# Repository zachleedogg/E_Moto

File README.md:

# E_Moto
Electric Motorcycle Project

This Repo Contains everything related to the E-Moto build.

Architecture inlcudes everything from block diagrams of the system level, design calculations, reseach link to off-the-shelf parts, and anything else that isn't strict design work.

CAD includes mechanical CAD files (mostly Solid Works) of various custom parts of the bike. Also includes some side-projects and also tools that are relevant to this project.

Firware is the Embeded code that targets the dsPIC33 processor used in the Electronics. I would like to switch to an STM32 based system but its a little late for that now.

Hardware is Electrical Hardware designs based on KiCad. There are more projects started than will probably be finished here but thats ok!

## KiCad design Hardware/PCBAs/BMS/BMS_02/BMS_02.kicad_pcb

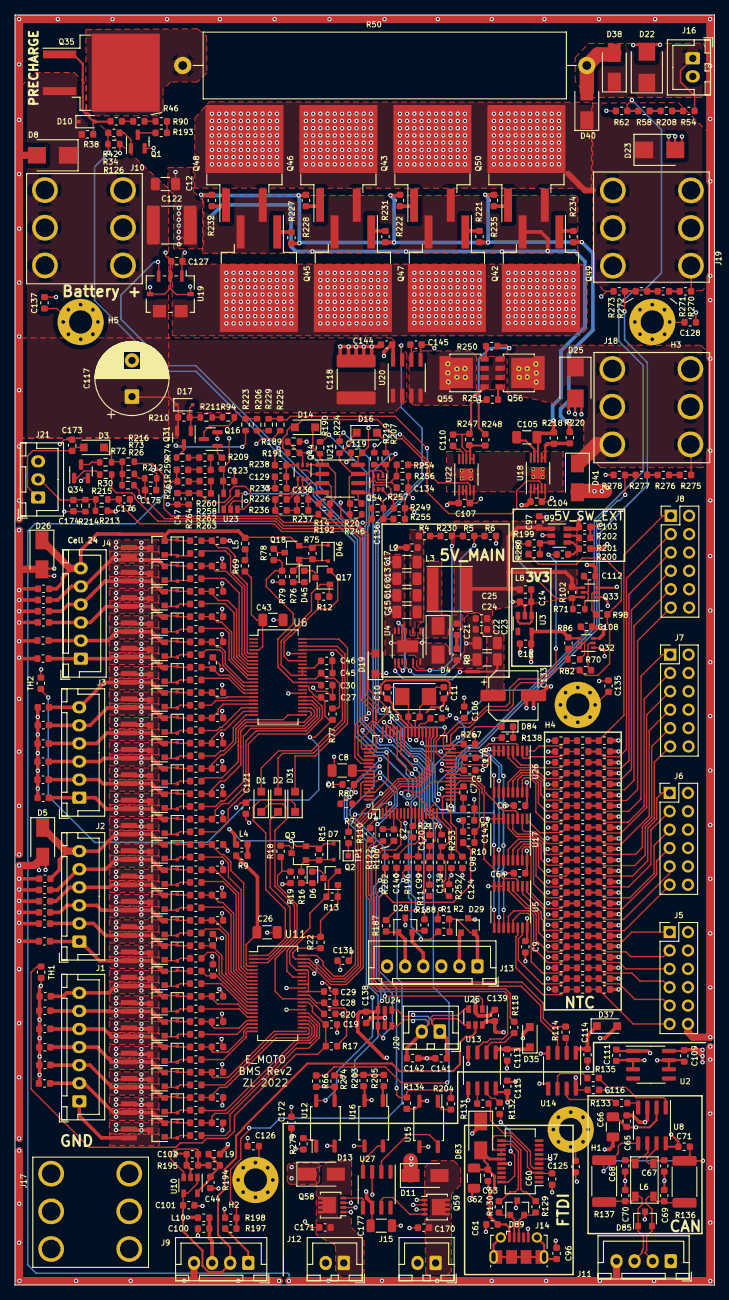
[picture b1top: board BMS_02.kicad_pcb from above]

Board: 4 copper layers, 96.7 x 175.6 mm, 621 parts (0 on the bottom side), 396 nets.

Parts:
C1, C2, C3, C4, C5, C6, C7, C9, C14, C18, C19, C20, C24, C27, C30, C31, C32, C33, C34, C35, C36, C37, C38, C39, C40, C41, C42, C44, C47, C48, C49, C50, C51, C52, C53, C54, C55, C56, C57, C58, C59, C60, C63, C64, C96, C97, C99, C101, C102, C103, C104, C107, C108, C109, C111, C112, C113, C114, C115, C116, C119, C123, C130, C136, C138, C139, C140, C141, C142, C143, C146, C147, C148, C149, C150, C151, C152, C153, C154, C155, C156, C157, C158, C159, C160, C161, C162, C163, C164, C165, C166, C167, C168, C169, C170, C171: 100nF; C_0603_1608Metric
C8, C22, C23, C105: 10uF; C_1206_3216Metric
C10, C11, C21, C67, C68, C69, C70, C145: 18pF; C_0603_1608Metric
C12, C13, C15, C16, C17, C26, C43: 100nF; C_1206_3216Metric
C25, C61, C65, C71, C72, C73, C74, C75, C76, C77, C78, C79, C80, C81, C82, C83, C84, C85, C86, C87, C88, C89, C90, C91, C92, C93, C94, C95, C98, C106, C120, C121, C124, C125, C126, C127, C128, C131, C132, C135, C137, C172, C173, C174, C175, C176, C178: 10nF; C_0603_1608Metric
C28, C29, C45, C46, C100, C110, C144: 1uF; C_0603_1608Metric
C62, C66, C177: 4u7; C_1206_3216Metric
C117: 22u; CP_Radial_D10.0mm_P5.00mm
C118, C122: 1u; C_2220_5650Metric
C129, C134: 1nF; C_0603_1608Metric
C133: 47u; CP_Elec_6.3x5.9
D1, D2, D3, D14, D16, D19, D31, D35, D37: D_Schottky; D_SOD-123F
D4, D11, D13, D38, D40, D41, D83: D_Schottky; D_SMA
D5, D26: D_TVS; D_SMA
D6, D45, D84: D_LED; D_0603_1608Metric
D7, D9, D10, D12, D15, D17, D18, D21, D24, D27, D30, D33, D36, D39, D42, D46, D48, D51, D54, D57, D60, D63, D66, D69, D72, D75, D78, D81: 12V; D_SOD-323F
D8, D22, D23, D25: D_TVS; D_SMB
D28, D29, D85, D89: D_Schottky_Dual_CommonAnode_AKK; D_SOT-23_ANK
H1, H2, H3, H4, H5: MountingHole_Pad; MountingHole_3.2mm_M3_Pad_Via
J1: Conn_01x07; JST_XH_B7B-XH-A_1x07_P2.50mm_Vertical
J2, J3, J4, J13: Conn_01x06; JST_XH_B6B-XH-A_1x06_P2.50mm_Vertical
J5, J6, J7, J8: Conn_02x06_Odd_Even; PinHeader_2x06_P2.54mm_Vertical
J9, J11: Conn_01x04; JST_XH_B4B-XH-A_1x04_P2.50mm_Vertical
J10, J17, J18, J19: 7807
J12, J15, J16, J20: Conn_01x02; JST_XH_B2B-XH-A_1x02_P2.50mm_Vertical
J14: USB_B_Micro; USB_Micro-B_Molex-105017-0001
J21: Conn_01x04; JST_XH_B3B-XH-A_1x03_P2.50mm_Vertical
L1, L2, L4, L5, L8, L9, L10: L_Ferrite; L_0603_1608Metric
L3: 47u; Inductor_Taiyo-Yuden_NR-60xx
L6: L_Coupled; ACT45B
NT1: Net-Tie_2; Net_Tie-0.5mm
Q1, Q2, Q16, Q17, Q34: Q_NMOS_GSD; SOT-23
Q3, Q4, Q5, Q6, Q7, Q8, Q9, Q10, Q11, Q12, Q13, Q14, Q15, Q18, Q19, Q20, Q21, Q22, Q23, Q24, Q25, Q26, Q27, Q28, Q29, Q30, Q31: Q_PMOS_GSD; SOT-23
Q32, Q33, Q44, Q54: Q_DUAL_NMOS_PMOS; SOT-363_SC-70-6
Q35: Q_PMOS_GDS; TO-263-2
Q42, Q43, Q45, Q46, Q47, Q48, Q49, Q50: NTB5D0N15MC; TO-263-2
Q55, Q56: TPH3300CNH,L1Q; POWER_SO8
Q58, Q59: RQ3G100GNTB; LFPAK33
R1, R2, R10, R12, R13, R15, R34, R66, R70, R71, R75, R80, R86, R102, R122, R126, R134, R139, R140, R141, R142, R143, R144, R145, R146, R147, R148, R149, R150, R151, R152, R153, R154, R155, R156, R157, R158, R159, R160, R161, R162, R163, R164, R165, R166, R167, R168, R169, R170, R171, R172, R173, R174, R175, R176, R177, R178, R179, R180, R181, R182, R183, R184, R185, R186, R189, R191, R192, R194, R195, R196, R197, R200, R201, R203, R207, R215, R217, R219, R226, R233, R237, R238, R246, R249, R253, R254, R255, R267, R274, R279, R280, R282: 10k0; R_0603_1608Metric
R3, R4, R14, R20, R54, R58, R74, R206, R208, R223, R225, R264, R270, R271, R272, R275, R276, R277: 1M; R_0603_1608Metric
R5, R16, R76: 32k0; R_0603_1608Metric
R6: 13k0; R_0603_1608Metric
R7, R23, R27, R30, R31, R35, R39, R43, R47, R51, R55, R59, R63, R67, R82, R83, R87, R91, R95, R98, R99, R103, R106, R107, R110, R111, R114, R115, R118, R119, R123, R127, R131, R132, R133, R135, R138, R187, R188, R199, R204, R205, R209: 100R; R_0603_1608Metric
R8, R202, R220, R221, R222, R227, R228, R231, R232, R234, R235, R248, R250, R251: 3R3; R_0603_1608Metric
R9, R69, R129, R130: 20R0; R_0603_1608Metric
R11, R198, R236, R252, R256: 19k6; R_0603_1608Metric
R17, R38, R42, R46, R62, R77, R90, R190, R193, R210, R216, R224, R229, R257, R273, R278: 100k; R_0603_1608Metric
R18, R78, R94, R211, R218, R230, R247: 499k; R_0603_1608Metric
R19, R79: 26k1 0.1%; R_0603_1608Metric
R21, R25, R29, R33, R37, R41, R45, R49, R53, R57, R61, R65, R81, R85, R89, R93, R97, R101, R105, R109, R113, R117, R121, R125: 15R0; Resistor_SMD_0805_Wide
R22: 1k8; R_0603_1608Metric
R24, R28, R32, R36, R40, R44, R48, R52, R56, R60, R64, R68, R84, R88, R92, R96, R100, R104, R108, R112, R116, R120, R124, R128: 3k3; R_0603_1608Metric
R26, R73: 4k7; R_0603_1608Metric
R50: 100R; R_Axial_Power_L50.0mm_W9.0mm_P55.88mm
R72, R212: 1k3; R_0603_1608Metric
R136, R137: 60R; R_2512_6332Metric
R213, R214: 330R; R_0603_1608Metric
R258, R259, R260, R261, R262, R263: 10M; R_0603_1608Metric
TH1, TH2: Thermistor_NTC; R_0603_1608Metric
TP1: TestPoint; TestPoint_Pad_1.0x1.0mm
U1: PIC33EP256MC506; TQFP-64_10x10mm_P0.5mm
U2: LM2931-5.0_SO8; SOIC-8_3.9x4.9mm_P1.27mm
U3: TPS73633DBV; SOT-23-5
U4: LTC3638; Linear_MSOP-12-16-1EP_3x4mm_P0.5mm
U5, U17, U26: CD4051B; TSSOP-16_4.4x5mm_P0.65mm
U6, U11: LTC6802-1; SSOP-44_5.3x12.8mm_P0.5mm
U7: FT231XS; SSOP-20_3.9x8.7mm_P0.635mm
U8: MCP2562-E-SN; SOIC-8_3.9x4.9mm_P1.27mm
U9: TPS2551-Q1; SOT-23-6
U10, U23: OPA320-Q1; SOT-23-5
U12, U15, U16: TLX9185A(GBTPL,F; SO-4_4.4x3.9mm_P2.54mm
U13, U14: ADUM1281ARZ-RL7; SOIC-8_3.9x4.9mm_P1.27mm
U18, U22: LTC7001; MSOP-10-1EP_3x3mm_P0.5mm_EP1.68x1.88mm_ThermalVias
U19: ACS72981LLRATR-100B5; Allegro_PSOF-7_4.8x6.4mm_P1.60mm
U20: CT415-HSN820DR; SOIC-8_3.9x4.9mm_P1.27mm
U21: LMV393; SOIC-8_3.9x4.9mm_P1.27mm
U24, U25: INA181; SOT-23-6
U27: FAN3216TMX-F085; SOIC-8_3.9x4.9mm_P1.27mm
Y1: 8MHz; Crystal_SMD_5032-2Pin_5.0x3.2mm

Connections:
5V_SW_nFAULT: R200.2, U1.31 (SDA2/RPI24/RA8)
12V_POWER: C109.1, D11.1 (K), D13.1 (K), J11.1, J12.2, J15.2, R279.2, U2.8 (IN)
12V_POWER_STATUS: R66.1, U1.42 (RD8)
+3.3VA: C108.1, C123.1, C138.1, C139.1, D35.2 (A), D37.2 (A), L9.2, Q32.3, Q44.4, Q54.4, R80.1, R122.1, R140.1, R142.1, R144.1, R146.1, R148.1, R150.1, R152.1, R154.1, R156.1, R158.1, R160.1, R162.1, R164.1, R166.1, R168.1, R170.1, R172.1, R174.1, R176.1, R178.1, R180.1, R182.1, R184.1, R186.1, R192.2, R201.1, R209.1, R226.2, R236.1, R246.2, R249.2, R255.1, U23.5 (Vcc), U24.6 (V+), U25.6 (V+)
+3V3: C1.1, C2.1, C3.1, C4.1, C5.1, C18.1, D19.1 (K), D29.2 (K), J13.2, L1.2, Q32.4, R1.1, R86.2, U1.10 (Vdd), U1.26 (Vdd), U1.38 (Vdd), U1.57 (Vdd), U3.5 (OUT), U12.4
+5V: C22.1, C23.1, C24.1, C25.1, C97.1, C133.1, L3.2, L8.2, NT1.2, Q33.4, R102.2, U9.1 (IN)
+5VA: C6.1, C9.1, C64.1, C104.1, C107.1, C112.1, C119.1, C127.1, C144.1, Q33.3, U5.16 (VDD), U17.16 (VDD), U18.1 (VCC), U19.1 (VCC), U20.8 (VCC), U21.8 (V+), U22.1 (VCC), U26.16 (VDD)
+5VL: C65.1, C66.2, C111.1, C115.1, C116.1, C177.2, D83.1 (K), U2.1 (OUT), U8.3 (VDD), U13.8 (VDD2), U14.8 (VDD2), U27.6 (VDD)
+5VP: C103.1, L10.2, R213.1, U9.6 (OUT)
+BATT: C12.1, C117.1, C118.1, C122.1, D8.1 (K), D10.1 (K), D17.1 (K), J10.1, L2.2, Q31.2 (S), Q35.3 (S), R38.2, R210.1, U19.5 (IP+), U20.1 (IP+), U20.2 (IP+)
/TopLevel/ChargerAndDCDC/HV_dcdc_gate: R248.2, R250.1, R251.1
/TopLevel/ChargerAndDCDC/HV_dcdc_shunt: Q55.5 (D), U20.3 (IP-), U20.4 (IP-)
/TopLevel/ChargerAndDCDC/HV_dcdc_source: C110.2, Q55.1 (S), Q55.2 (S), Q55.3 (S), Q56.1 (S), Q56.2 (S), Q56.3 (S), R247.2, U22.8 (TS)
/TopLevel/ChargerAndDCDC/HV_ev_g: R220.2, R221.1, R222.1, R227.1, R228.1, R231.1, R232.1, R234.1, R235.1
/TopLevel/ChargerAndDCDC/HV_ev_shunt: Q42.2 (D), Q45.2 (D), Q47.2 (D), Q49.2 (D), U19.6 (IP-)
/TopLevel/ChargerAndDCDC/HV_ev_source: C105.2, Q42.3 (S), Q43.3 (S), Q45.3 (S), Q46.3 (S), Q47.3 (S), Q48.3 (S), Q49.3 (S), Q50.3 (S), R218.2, U18.8 (TS)
/TopLevel/ChargerAndDCDC/dcdc_i: R253.1, R254.1, U20.7 (VIOUT)
/TopLevel/Communications/CAN_FILT_N: C68.2, L6.3, U8.6 (CANL)
/TopLevel/Communications/CAN_FILT_P: C67.2, L6.1, U8.7 (CANH)
/TopLevel/Contactor/HV_precharge_gate: D10.2 (A), Q35.1 (G), R38.1, R42.2
/TopLevel/Contactor/HV_precharge_switch: Q35.2 (D), R50.2
/TopLevel/Contactor/c1_in: U15.4, U27.2 (INA)
/TopLevel/Contactor/c1_out: Q59.4 (G), U27.7 (~OUTA)
/TopLevel/Contactor/c2_in: U16.4, U27.4 (INB)
/TopLevel/Contactor/c2_out: Q58.4 (G), U27.5 (~OUTB)
/TopLevel/IsolationDetection/HV_VBUS_ISO_SW: Q31.3 (D), R74.1, R206.2
/TopLevel/PowerRails/5V_N_SW_EN: Q33.6, R71.1, R102.1, R199.2
/TopLevel/PowerRails/FB_5V: NT1.1, U4.9 (VFB)
/TopLevel/PowerRails/HV_VBATT_FILT_5V_IN: C13.1, C15.1, C16.1, C17.1, L2.1, R4.1, U4.3 (VIN)
/TopLevel/PowerRails/SWITCH_NODE_5V: C21.1, D4.1 (K), L3.1, U4.1 (SW)
/TopLevel/Stack_1/5V_ref_LTC6802: C28.1, R17.2, U11.33 (Vref)
/TopLevel/Stack_1/Bank_1/C: C34.1, R35.1, U11.27 (C1)
/TopLevel/Stack_1/Bank_1/S: R36.1, U11.28 (S1)
/TopLevel/Stack_1/Bank_2/C: C33.1, R31.1, U11.25 (C2)
/TopLevel/Stack_1/Bank_2/S: R32.1, U11.26 (S2)
/TopLevel/Stack_1/Bank_3/C: C32.1, R27.1, U11.23 (C3)
/TopLevel/Stack_1/Bank_3/S: R28.1, U11.24 (S3)
/TopLevel/Stack_1/Bank_4/C: C31.1, R23.1, U11.21 (C4)
/TopLevel/Stack_1/Bank_4/S: R24.1, U11.22 (S4)
/TopLevel/Stack_1/Bank_5/C: C35.1, R39.1, U11.19 (C5)
/TopLevel/Stack_1/Bank_5/S: R40.1, U11.20 (S5)
/TopLevel/Stack_1/Bank_6/C: C36.1, R43.1, U11.17 (C6)
/TopLevel/Stack_1/Bank_6/S: R44.1, U11.18 (S6)
/TopLevel/Stack_1/Bank_7/C: C37.1, R47.1, U11.15 (C7)
/TopLevel/Stack_1/Bank_7/S: R48.1, U11.16 (S7)
/TopLevel/Stack_1/Bank_8/C: C38.1, R51.1, U11.13 (C8)
/TopLevel/Stack_1/Bank_8/S: R52.1, U11.14 (S8)
/TopLevel/Stack_1/Bank_9/S: R56.1, U11.12 (S9)
/TopLevel/Stack_1/Bank_10/C: C40.1, R59.1, U11.9 (C10)
/TopLevel/Stack_1/Bank_10/C-1: C39.1, R55.1, U11.11 (C9)
/TopLevel/Stack_1/Bank_10/S: R60.1, U11.10 (S10)
/TopLevel/Stack_1/Bank_11/C: C41.1, R63.1, U11.7 (C11)
/TopLevel/Stack_1/Bank_11/S: R64.1, U11.8 (S11)
/TopLevel/Stack_1/Bank_12/C: C42.1, R67.1, U11.5 (C12)
/TopLevel/Stack_1/Bank_12/S: R68.1, U11.6 (S12)
/TopLevel/Stack_1/SCBO: D31.1 (K), U11.1 (CSBO)
/TopLevel/Stack_1/SCKO: D1.1 (K), U11.3 (SCKO)
/TopLevel/Stack_1/SDIO: D2.1 (K), U11.2 (SDOI)
/TopLevel/Stack_1/Vreg: C29.1, Q2.1 (G), R13.1, R22.2, U11.34 (Vreg), U11.36 (MMB), U11.40 (Vmode)
/TopLevel/Stack_2/5V_ref_LTC6802: C45.1, R77.2, U6.33 (Vref)
/TopLevel/Stack_2/Bank_1/C: C51.1, R95.1, U6.27 (C1)
/TopLevel/Stack_2/Bank_1/S: R96.1, U6.28 (S1)
/TopLevel/Stack_2/Bank_2/C: C50.1, R91.1, U6.25 (C2)
/TopLevel/Stack_2/Bank_2/S: R92.1, U6.26 (S2)
/TopLevel/Stack_2/Bank_3/C: C49.1, R87.1, U6.23 (C3)
/TopLevel/Stack_2/Bank_3/S: R88.1, U6.24 (S3)
/TopLevel/Stack_2/Bank_4/C: C48.1, R83.1, U6.21 (C4)
/TopLevel/Stack_2/Bank_4/S: R84.1, U6.22 (S4)
/TopLevel/Stack_2/Bank_5/C: C52.1, R99.1, U6.19 (C5)
/TopLevel/Stack_2/Bank_5/S: R100.1, U6.20 (S5)
/TopLevel/Stack_2/Bank_6/C: C53.1, R103.1, U6.17 (C6)
/TopLevel/Stack_2/Bank_6/S: R104.1, U6.18 (S6)
/TopLevel/Stack_2/Bank_7/C: C54.1, R107.1, U6.15 (C7)
/TopLevel/Stack_2/Bank_7/S: R108.1, U6.16 (S7)
/TopLevel/Stack_2/Bank_8/C: C55.1, R111.1, U6.13 (C8)
/TopLevel/Stack_2/Bank_8/S: R112.1, U6.14 (S8)
/TopLevel/Stack_2/Bank_9/S: R116.1, U6.12 (S9)
/TopLevel/Stack_2/Bank_10/C: C57.1, R119.1, U6.9 (C10)
/TopLevel/Stack_2/Bank_10/C-1: C56.1, R115.1, U6.11 (C9)
/TopLevel/Stack_2/Bank_10/S: R120.1, U6.10 (S10)
/TopLevel/Stack_2/Bank_11/C: C58.1, R123.1, U6.7 (C11)
/TopLevel/Stack_2/Bank_11/S: R124.1, U6.8 (S11)
/TopLevel/Stack_2/Bank_12/C: C59.1, R127.1, U6.5 (C12)
/TopLevel/Stack_2/Bank_12/S: R128.1, U6.6 (S12)
/TopLevel/Stack_2/CSB: D31.2 (A), U6.44 (CSBI)
/TopLevel/Stack_2/SCK: D1.2 (A), U6.41 (SCKI)
/TopLevel/Stack_2/SDI: D2.2 (A), U6.42 (SDI)
/TopLevel/Stack_2/Vreg: C46.1, Q17.1 (G), R12.1, U6.34 (Vreg), U6.35 (TOS), U6.36 (MMB)
BANK_00: C19.2, C20.2, C26.1, C28.2, C29.2, C31.2, C32.2, C33.2, C34.2, C35.2, C36.2, C37.2, C38.2, C39.2, C40.2, C41.2, C42.2, C121.2, C131.1, C158.2, C159.2, C160.2, C161.2, C162.2, C163.2, C164.2, C165.2, C166.2, C167.2, C168.2, C169.2, D5.2 (A), J1.1, R19.2, R33.2, TH1.2, U11.29 (V-), U11.35 (TOS)
BANK_01: C169.1, D18.1 (K), J1.2, Q7.2 (S), R29.2, R35.2
BANK_02: C168.1, D15.1 (K), J1.3, Q6.2 (S), R25.2, R31.2
BANK_03: C167.1, D12.1 (K), J1.4, Q5.2 (S), R21.2, R27.2
BANK_04: C166.1, D9.1 (K), J1.5, Q4.2 (S), R23.2, R37.2
BANK_05: C165.1, D21.1 (K), J1.6, Q8.2 (S), R39.2, R41.2
BANK_06: C164.1, D24.1 (K), J1.7, Q9.2 (S), R43.2, R45.2
BANK_07: C163.1, D27.1 (K), J2.1, Q10.2 (S), R47.2, R49.2
BANK_08: C162.1, D30.1 (K), J2.2, Q11.2 (S), R51.2, R53.2
BANK_09: C161.1, D33.1 (K), J2.3, Q12.2 (S), R55.2, R57.2
BANK_10: C160.1, D36.1 (K), J2.4, Q13.2 (S), R59.2, R61.2
BANK_11: C159.1, D39.1 (K), J2.5, Q14.2 (S), R63.2, R65.2
BANK_12: C27.2, C30.2, C43.1, C45.2, C46.2, C48.2, C49.2, C50.2, C51.2, C52.2, C53.2, C54.2, C55.2, C56.2, C57.2, C58.2, C59.2, C121.1, C146.2, C147.2, C148.2, C149.2, C150.2, C151.2, C152.2, C153.2, C154.2, C155.2, C156.2, C157.2, C158.1, D5.1 (K), D7.1 (K), D26.2 (A), D42.1 (K), J2.6, L4.2, Q3.2 (S), Q15.2 (S), R15.1, R67.2, R79.2, R93.2, TH2.2, U6.29 (V-), U6.40 (Vmode)
BANK_13: C157.1, D57.1 (K), J3.1, Q22.2 (S), R89.2, R95.2
BANK_14: C156.1, D54.1 (K), J3.2, Q21.2 (S), R85.2, R91.2
BANK_15: C155.1, D51.1 (K), J3.3, Q20.2 (S), R81.2, R87.2
BANK_16: C154.1, D48.1 (K), J3.4, Q19.2 (S), R83.2, R97.2
BANK_17: C153.1, D60.1 (K), J3.5, Q23.2 (S), R99.2, R101.2
BANK_18: C152.1, D63.1 (K), J3.6, Q24.2 (S), R103.2, R105.2
BANK_19: C151.1, D66.1 (K), J4.1, Q25.2 (S), R107.2, R109.2
BANK_20: C150.1, D69.1 (K), J4.2, Q26.2 (S), R111.2, R113.2
BANK_21: C149.1, D72.1 (K), J4.3, Q27.2 (S), R115.2, R117.2
BANK_22: C148.1, D75.1 (K), J4.4, Q28.2 (S), R119.2, R121.2
BANK_23: C147.1, D78.1 (K), J4.5, Q29.2 (S), R123.2, R125.2
BANK_24: C146.1, D26.1 (K), D46.1 (K), D81.1 (K), J4.6, L5.2, Q18.2 (S), Q30.2 (S), R75.1, R127.2
CAN_N: C70.2, D85.2 (K), J11.3, L6.4, R137.1
CAN_P: C69.2, D85.3 (K), J11.2, L6.2, R136.2
CAN_RX: R114.2, U1.5 (RPI119/RG7)
CAN_RX_LV: R133.2, U14.7 (VIA)
CAN_TX: R106.2, R122.2, U1.4 (RP118/RG6)
CAN_TX_LV: R135.2, U14.6 (VOB)
CONTACTOR_PWM_1: R134.2, R204.2, U1.55 (RP57/RC9)
CONTACTOR_PWM_1_OUT: C170.1, D11.2 (A), J15.1, Q59.5 (D)
CONTACTOR_PWM_2: R203.2, R205.2, U1.52 (RP56/RC8)
CONTACTOR_PWM_2_OUT: C171.1, D13.2 (A), J12.1, Q58.5 (D)
DCDC_ENABLE: Q54.2, R207.1, R219.2, U1.46 (RP39/INT0/RB7)
DCDC_OUTPUT_CURRENT_AI: C132.1, R252.1, R253.2, U1.16 (PGEC3/VREF+/AN3/OA1OUT/RPI33/CTED1/RB1)
DCDC_OUTPUT_VOLTAGE_AI: C124.1, R277.1, R278.2, U1.18 (PGED1/AN5/C1IN1-/RP35/RB3)
DCDC_~FAULT: R224.2, U1.54 (RD6)
DEBUG_LED: D84.2 (A), U1.37 (SCL1/RPI53/RC5)
DEBUG_PIN: R7.1, U1.2 (RPI46/PWM1H/T3CK/RB14)
EV_CHARGER_CURRENT_AI: C120.1, R11.1, R217.1, U1.15 (PGED3/VREF-/AN2/C2IN1-/~SS1/RPI32/CTED2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)
EV_CHARGER_ENABLE: Q44.2, R189.2, R191.1, U1.48 (TCK/CVREF1O/ASCL1/RP40/T4CK/RB8)
EV_CHARGER_VOLTAGE_AI: C98.1, R272.1, R273.2, U1.17 (PGEC1/AN4/C1IN1+/RPI34/RB2)
EV_CHARGER_~FAULT: R190.2, U1.53 (RD5)
GND: C1.2, C2.2, C3.2, C4.2, C5.2, C6.2, C7.2, C8.2, C9.2, C10.2, C11.2, C12.2, C13.2, C14.2, C15.2, C16.2, C17.2, C18.2, C22.2, C23.2, C24.2, C25.2, C44.2, C47.2, C64.2, C72.2, C73.2, C74.2, C75.2, C76.2, C77.2, C78.2, C79.2, C80.2, C81.2, C82.2, C83.2, C84.2, C85.2, C86.2, C87.2, C88.2, C89.2, C90.2, C91.2, C92.2, C93.2, C94.2, C95.2, C97.2, C98.2, C99.2, C100.2, C101.2, C102.2, C103.2, C104.2, C106.2, C107.2, C113.2, C114.2, C117.2, C118.2, C119.2, C120.2, C122.2, C123.2, C124.2, C126.2, C127.2, C128.2, C129.2, C130.2, C131.2, C132.2, C133.2, C134.2, C135.2, C136.2, C137.2, C138.2, C139.2, C140.2, C141.2, C142.2, C143.2, C144.2, C145.2, C172.1, C173.1, C174.1, C175.1, C176.1, C178.2, D4.2 (A), D8.2 (A), D22.2 (A), D23.2 (A), D25.2 (A), D28.1 (A), D29.1 (A), J5.2, J5.4, J5.6, J5.8, J5.10, J5.12, J6.2, J6.4, J6.6, J6.8, J6.10, J6.12, J7.2, J7.4, J7.6, J7.8, J7.10, J7.12, J8.2, J8.4, J8.6, J8.8, J8.10, J8.12, J9.4, J13.3, J17.1, J21.3, Q1.2 (S), Q16.2 (S), Q32.1, Q33.1, Q34.2 (S), R6.2, R8.2, R11.2, R26.2, R62.1, R126.2, R134.1, R138.1, R189.1, R195.2, R198.1, R202.2, R203.1, R212.2, R214.2, R219.1, R229.1, R233.1, R237.2, R252.2, R256.2, R257.1, R264.2, R267.1, R273.1, R274.1, R278.1, U1.9 (Vss), U1.20 (AVss), U1.25 (Vss), U1.41 (Vss), U3.2 (GND), U4.6 (VPRG2), U4.8 (GND), U4.16 (GND), U4.17 (GND), U5.6 (INH), U5.7 (VEE), U5.8 (VSS), U9.2 (GND), U10.2 (GND), U13.4 (GND1), U14.4 (GND1), U15.2, U16.2, U17.6 (INH), U17.7 (VEE), U17.8 (VSS), U18.2 (Vcc_UV), U18.3 (GND), U18.5 (OVLO), U18.11 (GND), U19.2 (GND), U19.4 (NC), U19.7 (NC), U20.5 (GND), U21.4 (V-), U22.2 (Vcc_UV), U22.3 (GND), U22.5 (OVLO), U22.11 (GND), U23.2 (GND), U24.2 (GND), U24.5 (REF), U25.2 (GND), U26.6 (INH), U26.7 (VEE), U26.8 (VSS)
GND1: C60.2, C61.2, C62.2, C63.2, C65.2, C66.1, C67.1, C68.1, C69.1, C70.1, C71.2, C96.2, C109.2, C111.2, C115.2, C116.2, C125.2, C170.2, C171.2, C172.2, C177.1, D85.1 (A), D89.1 (A), J11.4, J14.5 (GND), Q58.1 (S), Q58.2 (S), Q58.3 (S), Q59.1 (S), Q59.2 (S), Q59.3 (S), R259.2, R261.1, U2.2 (GND), U2.3 (GND), U2.6 (GND), U2.7 (GND), U7.6 (GND), U7.16 (GND), U8.2 (VSS), U8.8 (STBY), U12.2, U13.5 (GND2), U14.5 (GND2), U15.3, U16.3, U27.3 (GND)
HIGH_CURRENT_SHUNT_AI: C143.1, R10.2, U1.21 (AN6/OA3OUT/C4IN1+/OCFB/RC0)
HV_BUS_VOLTAGE_AI: C106.1, R58.1, R62.2, U1.14 (AN1/C2IN1+/RA1)
HV_DCDC_OUTPUT: D25.1 (K), D41.1 (K), J18.1, Q56.5 (D), R275.2
HV_EV_CHARGER_INPUT: D23.1 (K), D40.1 (K), J19.1, Q43.2 (D), Q46.2 (D), Q48.2 (D), Q50.2 (D), R270.2
HV_PRECHARGE_OUT: D22.1 (K), D38.1 (K), J16.1, R54.2
ISOLATION_VOLTAGE_AI: U1.13 (AN0/OA2OUT/RA0), U23.1, U23.4 (-)
LOW_CURRENT_SHUNT_AI: C140.1, R282.2, U1.11 (AN10/RPI28/RA12)
MUX_1_AI: U1.23 (AN8/C3IN1+/~U1RTS/BCLK1/FLT3/RC2), U5.3 (X)
MUX_2_AI: U1.24 (AN11/C1IN2-(3)/~U1CTS/FLT4/RC11), U17.3 (X)
MUX_3_AI: U1.27 (AN12/C2IN2-(3)/~U2RTS/BCLK2/RE12), U26.3 (X)
MUX_A: U1.30 (AN15/RPI95/RE15), U5.11 (A), U17.11 (A), U26.11 (A)
MUX_B: U1.45 (RPI58/RC10), U5.10 (B), U17.10 (B), U26.10 (B)
MUX_C: U1.47 (RC13), U5.9 (C), U17.9 (C), U26.9 (C)
NTC_1_AI: C72.1, R139.2, U5.14 (X1)
NTC_1_OUT: J5.11, R139.1, R140.2
NTC_2_AI: C73.1, R141.2, U5.15 (X2)
NTC_2_OUT: J5.9, R141.1, R142.2
NTC_3_AI: C74.1, R143.2, U5.13 (X0)
NTC_3_OUT: J5.7, R143.1, R144.2
NTC_4_AI: C75.1, R145.2, U5.12 (X3)
NTC_4_OUT: J5.5, R145.1, R146.2
NTC_5_AI: C76.1, R147.2, U5.5 (X5)
NTC_5_OUT: J5.3, R147.1, R148.2
NTC_6_AI: C77.1, R149.2, U5.4 (X7)
NTC_6_OUT: J5.1, R149.1, R150.2
NTC_7_AI: C78.1, R151.2, U5.2 (X6)
NTC_7_OUT: J6.11, R151.1, R152.2
NTC_8_AI: C79.1, R153.2, U5.1 (X4)
NTC_8_OUT: J6.9, R153.1, R154.2
NTC_9_AI: C80.1, R155.2, U17.15 (X2)
NTC_9_OUT: J6.7, R155.1, R156.2
NTC_10_AI: C81.1, R157.2, U17.14 (X1)
NTC_10_OUT: J6.5, R157.1, R158.2
NTC_11_AI: C82.1, R159.2, U17.13 (X0)
NTC_11_OUT: J6.3, R159.1, R160.2
NTC_12_AI: C83.1, R161.2, U17.12 (X3)
NTC_12_OUT: J6.1, R161.1, R162.2
NTC_13_AI: C84.1, R163.2, U17.5 (X5)
NTC_13_OUT: J7.11, R163.1, R164.2
NTC_14_AI: C85.1, R165.2, U17.4 (X7)
NTC_14_OUT: J7.9, R165.1, R166.2
NTC_15_AI: C86.1, R167.2, U17.2 (X6)
NTC_15_OUT: J7.7, R167.1, R168.2
NTC_16_AI: C87.1, R169.2, U17.1 (X4)
NTC_16_OUT: J7.5, R169.1, R170.2
NTC_17_AI: C88.1, R171.2, U26.15 (X2)
NTC_17_OUT: J7.3, R171.1, R172.2
NTC_18_AI: C89.1, R173.2, U26.14 (X1)
NTC_18_OUT: J7.1, R173.1, R174.2
NTC_19_AI: C90.1, R175.2, U26.13 (X0)
NTC_19_OUT: J8.11, R175.1, R176.2
NTC_20_AI: C91.1, R177.2, U26.12 (X3)
NTC_20_OUT: J8.9, R177.1, R178.2
NTC_21_AI: C92.1, R179.2, U26.5 (X5)
NTC_21_OUT: J8.7, R179.1, R180.2
NTC_22_AI: C93.1, R181.2, U26.4 (X7)
NTC_22_OUT: J8.5, R181.1, R182.2
NTC_23_AI: C94.1, R183.2, U26.2 (X6)
NTC_23_OUT: J8.3, R183.1, R184.2
NTC_24_AI: C95.1, R185.2, U26.1 (X4)
NTC_24_OUT: J8.1, R185.1, R186.2
unnamed: C7.1, L1.1, U1.19 (AVdd)
unnamed: C8.1, U1.56 (Vcap)
unnamed: C10.1, R3.1, U1.40 (OSC2/CLKO/RC15), Y1.1
unnamed: C11.1, R3.2, U1.39 (OSC1/CLKI/RC12), Y1.2
unnamed: C14.1, L8.1, U3.1 (IN), U3.3 (EN)
unnamed: C19.1, R17.1, TH1.1, U11.31 (Vtemp1)
unnamed: C20.1, R18.2, R19.1, U11.32 (Vtemp2)
unnamed: C21.2, R8.1
unnamed: C26.2, R9.1, U11.4 (V+)
unnamed: C27.1, R77.1, TH2.1, U6.31 (Vtemp1)
unnamed: C30.1, R78.2, R79.1, U6.32 (Vtemp2)
unnamed: C43.2, R69.1, U6.4 (V+)
unnamed: C44.1, L9.1, R194.1, U10.5 (Vcc)
unnamed: C47.1, R263.2, R264.1, U23.3 (+)
unnamed: C60.1, U7.3 (VCCIO), U7.13 (3V3OUT), U7.14 (~RESET)
unnamed: C71.1, R136.1, R137.2, U8.5 (SPLIT)
unnamed: C96.1, J14.6 (Shield)
unnamed: C102.1, R194.2, R195.1, U10.3 (+)
unnamed: C105.1, U18.9 (BST)
unnamed: C108.2, Q32.5, R70.1
unnamed: C110.1, U22.9 (BST)
unnamed: C112.2, Q33.5, R71.2
unnamed: C113.1, D35.1 (K), U13.1 (VDD1)
unnamed: C114.1, D37.1 (K), U14.1 (VDD1)
unnamed: C125.1, H1.1
unnamed: C126.1, H2.1
unnamed: C128.1, H3.1
unnamed: C129.1, Q44.3, R233.2, R238.2, U21.2 (-)
unnamed: C130.1, R14.2, R236.2, R237.1, U21.3 (+)
unnamed: C134.1, Q54.3, R254.2, R256.1, U21.6 (-)
unnamed: C135.1, H4.1
unnamed: C136.1, R20.2, R255.2, R257.2, U21.5 (+)
unnamed: C137.1, H5.1
unnamed: C145.1, U20.6 (FILTER)
unnamed: D3.1 (K), R26.1, R72.1, R73.1, R216.1
unnamed: D6.1 (K), Q2.3 (D)
unnamed: D6.2 (A), R16.2
unnamed: D7.2 (A), Q3.1 (G), R15.2, R16.1
unnamed: D9.2 (A), Q4.1 (G), R24.2
unnamed: D12.2 (A), Q5.1 (G), R28.2
unnamed: D14.1 (K), Q44.1, R14.1, R190.1, R192.1, U21.1
unnamed: D14.2 (A), R191.2, U18.4 (INP)
unnamed: D15.2 (A), Q6.1 (G), R32.2
unnamed: D16.1 (K), Q54.1, R20.1, R224.1, R246.1, U21.7
unnamed: D16.2 (A), R207.2, U22.4 (INP)
unnamed: D17.2 (A), Q31.1 (G), R210.2, R211.1
unnamed: D18.2 (A), Q7.1 (G), R36.2
unnamed: D21.2 (A), Q8.1 (G), R40.2
unnamed: D24.2 (A), Q9.1 (G), R44.2
unnamed: D27.2 (A), Q10.1 (G), R48.2
unnamed: D28.2 (K), J13.5, R187.1
unnamed: D28.3 (K), J13.4, R188.1
unnamed: D30.2 (A), Q11.1 (G), R52.2
unnamed: D33.2 (A), Q12.1 (G), R56.2
unnamed: D36.2 (A), Q13.1 (G), R60.2
unnamed: D38.2 (A), D40.2 (A), D41.2 (A), R50.1
unnamed: D39.2 (A), Q14.1 (G), R64.2
unnamed: D42.2 (A), Q15.1 (G), R68.2
unnamed: D45.1 (K), Q17.3 (D)
unnamed: D45.2 (A), R76.2
unnamed: D46.2 (A), Q18.1 (G), R75.2, R76.1
unnamed: D48.2 (A), Q19.1 (G), R84.2
unnamed: D51.2 (A), Q20.1 (G), R88.2
unnamed: D54.2 (A), Q21.1 (G), R92.2
unnamed: D57.2 (A), Q22.1 (G), R96.2
unnamed: D60.2 (A), Q23.1 (G), R100.2
unnamed: D63.2 (A), Q24.1 (G), R104.2
unnamed: D66.2 (A), Q25.1 (G), R108.2
unnamed: D69.2 (A), Q26.1 (G), R112.2
unnamed: D72.2 (A), Q27.1 (G), R116.2
unnamed: D75.2 (A), Q28.1 (G), R120.2
unnamed: D78.2 (A), Q29.1 (G), R124.2
unnamed: D81.2 (A), Q30.1 (G), R128.2
unnamed: D84.1 (K), R138.2
unnamed: L4.1, R9.2
unnamed: L5.1, R69.2
unnamed: Q1.1 (G), R34.1
unnamed: Q1.3 (D), R193.1
unnamed: Q2.2 (S), R13.2, U11.38 (GPIO1)
unnamed: Q3.3 (D), R18.1
unnamed: Q4.3 (D), R21.1
unnamed: Q5.3 (D), R25.1
unnamed: Q6.3 (D), R29.1
unnamed: Q7.3 (D), R33.1
unnamed: Q8.3 (D), R37.1
unnamed: Q9.3 (D), R41.1
unnamed: Q10.3 (D), R45.1
unnamed: Q11.3 (D), R49.1
unnamed: Q12.3 (D), R53.1
unnamed: Q13.3 (D), R57.1
unnamed: Q14.3 (D), R61.1
unnamed: Q15.3 (D), R65.1
unnamed: Q16.1 (G), R209.2
unnamed: Q16.3 (D), R94.2
unnamed: Q17.2 (S), R12.2, U6.38 (GPIO1)
unnamed: Q18.3 (D), R78.1
unnamed: Q19.3 (D), R81.1
unnamed: Q20.3 (D), R85.1
unnamed: Q21.3 (D), R89.1
unnamed: Q22.3 (D), R93.1
unnamed: Q23.3 (D), R97.1
unnamed: Q24.3 (D), R101.1
unnamed: Q25.3 (D), R105.1
unnamed: Q26.3 (D), R109.1
unnamed: Q27.3 (D), R113.1
unnamed: Q28.3 (D), R117.1
unnamed: Q29.3 (D), R121.1
unnamed: Q30.3 (D), R125.1
unnamed: Q32.2, R82.1
unnamed: Q32.6, R70.2, R86.1
unnamed: Q33.2, R98.1
unnamed: Q34.1 (G), R30.1
unnamed: Q34.3 (D), R72.2
unnamed: Q42.1 (G), R221.2
unnamed: Q43.1 (G), R222.2
unnamed: Q44.5, Q44.6, R226.1
unnamed: Q45.1 (G), R227.2
unnamed: Q46.1 (G), R228.2
unnamed: Q47.1 (G), R231.2
unnamed: Q48.1 (G), R232.2
unnamed: Q49.1 (G), R234.2
unnamed: Q50.1 (G), R235.2
unnamed: Q54.5, Q54.6, R249.1
unnamed: Q55.4 (G), R250.2
unnamed: Q56.4 (G), R251.2
unnamed: R2.1, U1.7 (~MCLR)
unnamed: R5.2, R6.1, U4.12 (OVLO)
unnamed: R7.2, TP1.1
unnamed: R10.1, U24.1
unnamed: R42.1, R46.2
unnamed: R46.1, R90.2
unnamed: R106.1, U14.3 (VIB)
unnamed: R110.1, U13.3 (VIB)
unnamed: R114.1, U14.2 (VOA)
unnamed: R118.1, U13.2 (VOA)
unnamed: R129.2, U7.11 (USBDP)
unnamed: R130.2, U7.12 (USBDM)
unnamed: R131.2, U7.4 (RXD)
unnamed: R132.2, U7.20 (TXD)
unnamed: R133.1, U8.4 (RXD)
unnamed: R135.1, U8.1 (TXD)
unnamed: R90.1, R193.2
unnamed: R196.1, R197.1, R198.2
unnamed: R199.1, R280.1, U9.3 (EN)
unnamed: R200.1, R201.2, U9.4 (FAULT)
unnamed: R202.1, U9.5 (ILIM)
unnamed: R204.1, U15.1
unnamed: R205.1, U16.1
unnamed: R206.1, R223.2
unnamed: R58.2, R208.1
unnamed: R54.1, R208.2
unnamed: R94.1, R211.2
unnamed: R217.2, R238.1, U19.3 (VOUT)
unnamed: R218.1, R220.1, U18.6 (TGUP), U18.7 (TGDN)
unnamed: R223.1, R225.2
unnamed: R4.2, R230.1
unnamed: R5.1, R230.2, U4.14 (RUN)
unnamed: R247.1, R248.1, U22.6 (TGUP), U22.7 (TGDN)
unnamed: R258.1, R260.2
unnamed: R258.2, R259.1
unnamed: R74.2, R260.1
unnamed: R261.2, R262.1
unnamed: R262.2, R263.1
unnamed: R270.1, R271.2
unnamed: R271.1, R272.2
unnamed: R66.2, R274.2, U12.3
unnamed: R275.1, R276.2
unnamed: R276.1, R277.2
unnamed: R279.1, U12.1
unnamed: R282.1, U25.1
unnamed: U4.7 (VPRG1), U4.10 (SS)
PGEC: R187.2, U1.44 (PGEC2/ASCL2/RP38/RB6)
PGED: R188.2, U1.43 (PGED2/ASDA2/RP37/RB5)
PILOT: C173.2, D3.2 (A), J21.1
PILOT_EN: R30.2, U1.50 (RP54/RC6)
PILOT_MONITOR_AI: C175.2, R73.2, R212.1, U1.28 (AN13/C3IN2-(3)/~U2CTS/RE13)
PILOT_MONITOR_PWM_IN: D19.2 (A), R216.2, U1.51 (RP55/RC7)
PRE_CHARGE_EN: R34.2, R126.1, U1.62 (RPI44/PWM2H/RB12)
PROXIMITY: C174.2, J21.2, R213.2, R214.1, R215.2
PROXIMITY_MONITOR_AI: C176.2, R215.1, U1.22 (AN7/C3IN1-/C4IN1-/RC1)
SHUNT_N: C141.1, J20.1, U24.4 (-), U25.4 (-)
SHUNT_P: C142.1, J20.2, U24.3 (+), U25.3 (+)
SPI_CKL: U1.35 (SCK1/RPI51/RC3), U11.41 (SCKI)
SPI_CS: U1.36 (SDA1/RPI52/RC4), U11.44 (CSBI)
SPI_MIPO: R22.1, U1.34 (SDI1/RPI25/RA9), U11.43 (SDO)
SPI_MOPI: U1.33 (CVREF2O/SDO1/RP20/T1CK/RA4), U11.42 (SDI)
SW_EN: R82.2, R98.2, R267.2, R280.2, U1.32 (FLT32/SCL2/RP36/RB4)
Transducer_Input: J9.1, R197.2
Transducer_Input_AI: C99.1, R196.2, U1.12 (AN9/RPI27/RA11)
Transducer_Pwr: C100.1, J9.3, L10.1
Transducer_Ref: C101.1, J9.2, U10.1, U10.4 (-), U25.5 (REF)
UART_RX: R118.2, U1.58 (RPI96/RF0)
UART_RX_LV: R132.1, U13.7 (VIA)
UART_TX: R80.2, R110.2, U1.59 (RP97/RF1)
UART_TX_LV: R131.1, U13.6 (VOB)
USB_5V: C61.1, C62.1, C63.1, D83.2 (A), J14.1 (VBUS), U7.15 (VCC)
USB_D+: D89.3 (K), J14.3 (D+), R129.1
USB_D-: D89.2 (K), J14.2 (D-), R130.1
VBUS_VOLTAGE_AI: C178.1, R225.1, R229.2, U1.29 (AN14/RPI94/RE14)
nRESET: D29.3 (K), J13.1, R1.2, R2.2

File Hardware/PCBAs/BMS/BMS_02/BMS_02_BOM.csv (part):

"Reference","Value","Footprint","Datasheet","Alternate","DNP","Digikey_PN","MPN","Mouser_PN","Part Number","PartNumber","Voltage","populate","Qty"
"C1-C7, C9, C14, C18-C20, C24, C27, C30-C42, C44, C47-C60, C63, C64, C96, C97, C99, C101-C104, C107-C109, C111-C116, C119, C123, C130, C136, C138-C143, C146-C171","100nF","Capacitor_SMD:C_0603_1608Metric","http://psearch.en.murata.com/capacitor/product/GCM188R71H104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","","-- mixed values --","490-4779-1-ND","GCM188R71H104KA57D","","GCM188R71H104KA57D","","-- mixed values --","-- mixed values --","96"
"C8, C22, C23, C105","10uF","Capacitor_SMD:C_1206_3216Metric","","","-- mixed values --","1276-6797-1-ND","CL31B106KOHVPNE","","CL31B106KOHVPNE","","-- mixed values --","","4"
"C10, C11, C21, C67-C70, C145","18pF","Capacitor_SMD:C_0603_1608Metric","https://product.tdk.com/info/en/documents/chara_sheet/CGA3E2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","","-- mixed values --","445-5631-1-ND","CGA3E2C0G1H180J080AA","","CGA3E2C0G1H180J080AA","","-- mixed values --","-- mixed values --","8"
"C12, C13, C15-C17, C26, C43","100nF","Capacitor_SMD:C_1206_3216Metric","https://product.tdk.com/info/en/documents/chara_sheet/CGA5L3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","","","445-5851-1-ND","CGA5L3X7R2E104K160AA","","CGA5L3X7R2E104K160AA","","","","7"
"C25, C61, C65, C71-C95, C98, C106, C120, C121, C124-C128, C131, C132, C135, C137, C172-C176, C178","10nF","Capacitor_SMD:C_0603_1608Metric","~","","","490-4781-1-ND","GCM188R72A103KA37D","","GCM188R72A103KA37D","","","-- mixed values --","47"
"C28, C29, C45, C46, C100, C110, C144","1uF","Capacitor_SMD:C_0603_1608Metric","https://product.tdk.com/system/files/dam/doc/product/capacit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","","","445-12539-1-ND","","","CGA3E1X7R1C105K080AC","","","","7"
"C62, C66, C177","4u7","Capacitor_SMD:C_1206_3216Metric","https://product.tdk.com/info/en/catalog/datasheets/mlcc_auto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","","","445-172481-1-ND","CGA5L3X7R1H475K160AE","","CGA5L3X7R1H475K160AE","","","y","3"
"C117","22u","Capacitor_THT:CP_Radial_D10.0mm_P5.00mm","https://www.nichicon.co.jp/english/products/pdfs/e-ucs.pdf","","","493-14364-ND","","","UCS2C220MPD","","","","1"
"C118, C122","1u","Capacitor_SMD:C_2220_5650Metric","https://product.tdk.com/info/en/documents/chara_sheet/C5750X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","","","445-4532-1-ND","","","C5750X7R2E105M230KA","","","","2"
"C129, C134","1nF","Capacitor_SMD:C_0603_1608Metric","https://product.tdk.com/system/files/dam/doc/product/capacit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","","","445-5659-1-ND","CGA3E2X7R1H102K080AA","","CGA3E2X7R1H102K080AA","","","","2"
"C133","47u","Capacitor_SMD:CP_Elec_6.3x5.9","https://www.rubycon.co.jp/wp-content/uploads/catalog-aluminu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","","","1189-16SLV47M6.3X6.1CT-ND","","","16SLV47M6.3X6.1","","","","1"
"D1-D3, D14, D16, D19, D31, D35, D37","D_Schottky","Diode_SMD:D_SOD-123F","https://www.onsemi.com/pub/Collateral/RS1AFA-D.PDF","","","S215FACT-ND","RS1GFA","","RS1GFA","","","","9"
"D4, D11, D13, D38, D40, D41, D83","D_Schottky","Diode_SMD:D_SMA","https://www.st.com/content/ccc/resource/technical/document/d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","","","497-7545-1-ND","STPS1150A","","STPS1150A","","","-- mixed values --","7"
"D5, D26","D_TVS","Diode_SMD:D_SMA","https://www.diodes.com/assets/Datasheets/SMAJ5.0CA-SMAJ200CA.pdf","","","SMAJ60A-FDICT-ND","","","SMAJ60A-13-F","","","","2"
"D6, D45, D84","D_LED","Diode_SMD:D_0603_1608Metric","http://optoelectronics.liteon.com/upload/download/DS22-2000-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","","","160-1447-1-ND","LTST-C191KRKT","","LTST-C191KRKT","","","-- mixed values --","3"
"D7, D9, D10, D12, D15, D17, D18, D21, D24, D27, D30, D33, D36, D39, D42, D46, D48, D51, D54, D57, D60, D63, D66, D69, D72, D75, D78, D81","12V","Diode_SMD:D_SOD-323F","https://www.onsemi.com/pdf/datasheet/mm3z9v1c-d.pdf","","","MM3Z12VCCT-ND","MM3Z12VC","","MM3Z12VC","","","","28"
"D8, D22, D23, D25","D_TVS","Diode_SMD:D_SMB","https://www.diodes.com/assets/Datasheets/ds19002.pdf","","","SMBJ120A-FDICT-ND","","","SMBJ120A-13-F","","","","4"
"D28, D29, D85, D89","D_Schottky_Dual_CommonAnode_AKK","Footprints:D_SOT-23_ANK","https://media.digikey.com/pdf/Data%20Sheets/ST%20Microelectr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,24)-2BLY,.pdf","","","1727-5397-1-ND","ESDCAN24-2BLY","","ESDCAN24-2BLY","","","","4"
"H1-H5","MountingHole_Pad","Footprints:MountingHole_3.2mm_M3_Pad_Via","~","","","","","","","","","","5"
"J1","Conn_01x07","Connector_JST:JST_XH_B7B-XH-A_1x07_P2.50mm_Vertical","~","","","","","","","","","","1"
"J2-J4, J13","Conn_01x06","Connector_JST:JST_XH_B6B-XH-A_1x06_P2.50mm_Vertical","~","","-- mixed values --","","","","","","","","4"
"J5-J8","Conn_02x06_Odd_Even","Connector_PinHeader_2.54mm:PinHeader_2x06_P2.54mm_Vertical","~","","","","","","","","","","4"
"J9, J11","Conn_01x04","Connector_JST:JST_XH_B4B-XH-A_1x04_P2.50mm_Vertical","~","","","","","","","","","","2"
"J10, J17-J19","7807","Footprints:7807","https://www.keyelco.com/userAssets/file/M65p69.pdf","","","36-7807-ND ","7807","","7807","","","","4"
"J12, J15, J16, J20","Conn_01x02","Connector_JST:JST_XH_B2B-XH-A_1x02_P2.50mm_Vertical","~","","","","","","","","","","4"
"J14","USB_B_Micro","Connector_USB:USB_Micro-B_Molex-105017-0001","~",""," ","","","","","","","","1"
"J21","Conn_01x04","Connector_JST:JST_XH_B3B-XH-A_1x03_P2.50mm_Vertical","~","","","","","","","","","","1"
"L1, L2, L4, L5, L8-L10","L_Ferrite","Inductor_SMD:L_0603_1608Metric","https://www.we-online.com/katalog/datasheet/742792609.pdf","","-- mixed values --","732-1591-1-ND","742792609","","742792609","","","","7"
"L3","47u","Inductors:Inductor_Taiyo-Yuden_NR-60xx","https://www.yuden.co.jp/productdata/catalog/wound04_e.pdf","","","587-2104-1-ND","NR6028T470M","","NR6028T470M","","","","1"
"L6","L_Coupled","Footprints:ACT45B","https://en.tdk.eu/inf/30/ds/act45b.pdf","","","495-4597-1-ND","B82787C0513H002","","B82787C0513H002","","","y","1"
"NT1","Net-Tie_2","Footprints:Net_Tie-0.5mm","~","","","","","","","","","","1"
"Q1, Q2, Q16, Q17, Q34","Q_NMOS_GSD","Package_TO_SOT_SMD:SOT-23","https://ww1.microchip.com/downloads/en/DeviceDoc/TN5335-N-Ch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","","","TN5335K1-GCT-ND","TN5335K1-G","","TN5335K1-G","","","","5"
"Q3-Q15, Q18-Q31","Q_PMOS_GSD","Package_TO_SOT_SMD:SOT-23","-- mixed values --","","","-- mixed values --","-- mixed values --","","-- mixed values --","","","","27"
"Q32, Q33, Q44, Q54","Q_DUAL_NMOS_PMOS","Package_TO_SOT_SMD:SOT-363_SC-70-6","https://fscdn.rohm.com/en/products/databook/datasheet/discre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","","","US6M2CT-ND","US6M2TR","","US6M2TR","","","","4"
"Q35","Q_PMOS_GDS","Package_TO_SOT_SMD:TO-263-2","https://www.onsemi.com/pdf/datasheet/fqb12p20-d.pdf","","","FQB12P20TMCT-ND","FQB12P20TM","","FQB12P20TM","","","","1"
"Q42, Q43, Q45-Q50","NTB5D0N15MC","Package_TO_SOT_SMD:TO-263-2","https://www.mouser.com/datasheet/2/308/1/NTB5D0N15MC_D-2318612.pdf","","","","NTB5D0N15MC","863-NTB5D0N15MC","NTB5D0N15MC","","","","8"
"Q55, Q56","TPH3300CNH,L1Q","Footprints:POWER_SO8","-- mixed values --","","","TPH3300CNHL1QCT-ND","TPH3300CNH,L1Q","","TPH3300CNH,L1Q","","","","2"
"Q58, Q59","RQ3G100GNTB","Package_TO_SOT_SMD:LFPAK33","https://fscdn.rohm.com/en/products/databook/datasheet/discre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","","","RQ3G100GNTBCT-ND","RQ3G100GNTB","","RQ3G100GNTB","","","","2"
"R1, R2, R10, R12, R13, R15, R34, R66, R70, R71, R75, R80, R86, R102, R122, R126, R134, R139-R186, R189, R191, R192, R194-R197, R200, R201, R203, R207, R215, R217, R219, R226, R233, R237, R238, R246, R249, R253-R255, R267, R274, R279, R280, R282","10k0","Resistor_SMD:R_0603_1608Metric","http://www.yageo.com/NewPortal/yageodocoutput?fileName=/pdf/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","","-- mixed values --","311-10KLDCT-ND","AC0603FR-0710KL","","AC0603FR-0710KL","","","","93"
"R3, R4, R14, R20, R54, R58, R74, R206, R208, R223, R225, R264, R270-R272, R275-R277","1M","Resistor_SMD:R_0603_1608Metric","http://www.yageo.com/NewPortal/yageodocoutput?fileName=/pdf/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","","-- mixed values --","311-1MLDCT-ND","AC0603FR-071ML","","AC0603FR-071ML","","","","18"
"R5, R16, R76","32k0","Resistor_SMD:R_0603_1608Metric","https://media.digikey.com/pdf/Data%20Sheets/KOA%20Speer/RN73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","","","2019-RN73R1JTTD3202B25CT-ND","RN73R1JTTD3202B25","","RN73R1JTTD3202B25","","","","3"
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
